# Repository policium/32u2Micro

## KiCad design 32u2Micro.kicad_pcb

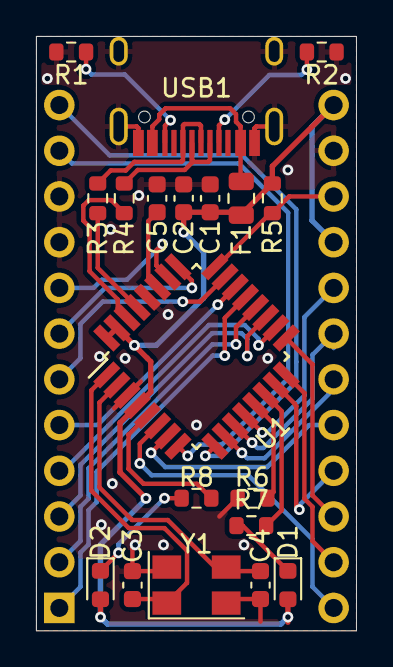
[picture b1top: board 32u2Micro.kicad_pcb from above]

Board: 2 copper layers, 17.8 x 33.0 mm, 21 parts (0 on the bottom side), 36 nets.

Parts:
C1: 10u; C_0603_1608Metric
C2: 0.1u; C_0603_1608Metric
C3, C4: 22p; C_0603_1608Metric
C5: 1u; C_0603_1608Metric
D1: BLUE; LED_0603_1608Metric
D2: GREEN; LED_0603_1608Metric
F1: 500m; Fuse_0805_2012Metric
J1, J2: Conn_01x12; PinHeader_1x12_P2.54mm_Vertical
R1, R2: 5.1k; R_0603_1608Metric
R3, R4: 22; R_0603_1608Metric
R5, R6: 4.7k; R_0603_1608Metric
R7, R8: R_Small; R_0603_1608Metric
U1: ATmega32U2-AU; TQFP-32_7x7mm_P0.8mm
USB1: HRO-TYPE-C-31-M-12
Y1: 16MHz; Crystal_SMD_5032-4Pin_5.0x3.2mm

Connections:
/A0: J2.8, U1.7
/A1: J2.7, U1.10
/A2: J2.6, U1.11
/A3: J2.5, U1.12
/D2: J1.8, U1.26
/D3: J1.7, U1.25
/D4: J1.6, U1.23
/D5: J1.5, U1.22
/D6: J1.4, U1.18
/D7: J1.3, U1.19
/D8: J1.2, U1.20
/D9: J1.1, U1.21
/D10: J2.12, U1.6
/MISO: J2.10, U1.17
/MOSI: J2.11, U1.16
/RESET: J2.3, R5.2, U1.24
/RXI: J1.11, U1.8
/SCK: J2.9, U1.15
/TXO: J1.12, U1.9
GND: C1.2, C2.2, C3.2, C4.1, C5.2, J1.9, J1.10, J2.2, R1.1, R2.2, R6.1, U1.3, U1.28, USB1.1, USB1.12, USB1.13, Y1.2, Y1.4
unnamed: C3.1, U1.1, Y1.1
unnamed: C4.2, U1.2, Y1.3
unnamed: C5.1, U1.27
unnamed: D1.1, R7.1
unnamed: D2.1, R8.1
unnamed: F1.1, USB1.2, USB1.11
unnamed: R1.2, USB1.10
unnamed: R2.1, USB1.4
unnamed: R3.1, U1.29
unnamed: R3.2, USB1.6, USB1.8
unnamed: R4.1, USB1.5, USB1.7
unnamed: R4.2, U1.30
unnamed: R6.2, U1.13
unnamed: R7.2, U1.14
unnamed: R8.2, U1.5
VBUS: C1.1, C2.1, D1.2, D2.2, F1.2, J2.1, J2.4, R5.1, U1.4, U1.31, U1.32
